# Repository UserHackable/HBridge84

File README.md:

# User Hackable HBridge84 Project

This is the User Hackable HBridge84 Project. 

It's purpose is to be a compact driver board for cars or robots. 

## Brains

The microcontroller used by this project is the ATtiny84 chip manufactured by Atmel. 
To program this chip using the [Arduino environment](https://www.arduino.cc/en/Main/Software), you will first need the [ATtiny board definition file](http://highlowtech.org/?p=1695) from [High Low Tech](http://highlowtech.org/). 

It includes:

* a C++ library for the Arduino IDE
* the Eagle Cad schematic and board layout files

# Arduino Installation

1. Start with a recent install of the [Arduino IDE](https://www.arduino.cc/en/Main/Software).
2. Install the [ATtiny library from High Low Tech](http://highlowtech.org/?p=1695).
3. Make sure you have an AVR ICSP programmer like the [Sparkfun Pocket AVR Programmer](https://www.sparkfun.com/products/9825) with it's drivers installed. 
4. Install this library by placing this entire folder as a subfolder in your Arduino/libraries folder.

## HBridge84 

### Board dimensions

* (200000, 130000) original units
* (2.0000, 1.3000) inches
* (50.8000, 33.0200) mm

| Front | Back |
| --- | --- |
|  |  |

## RJ11Breakout 

### Board dimensions

* (70000, 70000) original units
* (0.7000, 0.7000) inches
* (17.7800, 17.7800) mm

| Front | Back |
| --- | --- |
|  |  |

## RJ11-ICSP-Breakout 

### Board dimensions

* (90000, 100000) original units
* (0.9000, 1.0000) inches
* (22.8600, 25.4000) mm

| Front | Back |
| --- | --- |
|  |  |

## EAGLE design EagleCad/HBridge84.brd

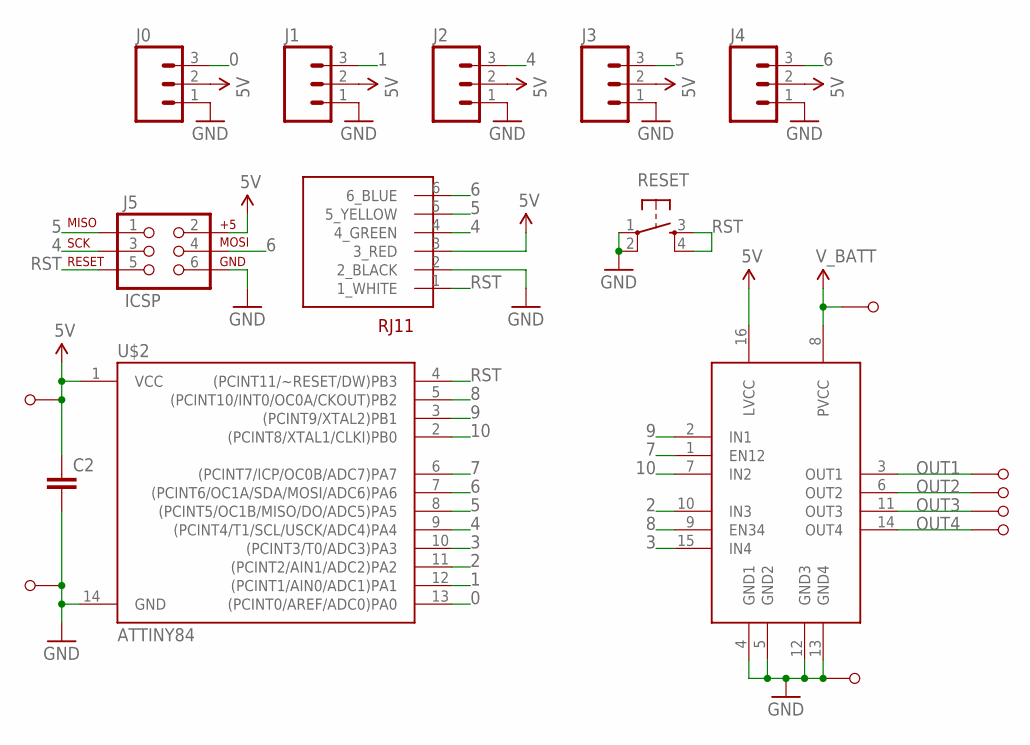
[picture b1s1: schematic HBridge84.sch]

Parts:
C2: CAPPTH; CAP-PTH-SMALL
J0, J1, J2, J3, J4: M03PTH; 1X03
J5: ICSP; 2X3-NS
RESET: TAC_SWITCHPTH; TACTILE-PTH
SN754410: SN754410; DIP16
U$1, U$3, U$4, U$5, U$6, U$8, U$9, U$10: M1; M1_NO_STRAIN
U$2: ATTINY84; DIL14
U$7: RJ12

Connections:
0: J0.3, U$2.13 ((PCINT0/AREF/ADC0)PA0)
1: J1.3, U$2.12 ((PCINT1/AIN0/ADC1)PA1)
2: SN754410.10 (IN3), U$2.11 ((PCINT2/AIN1/ADC2)PA2)
3: SN754410.15 (IN4), U$2.10 ((PCINT3/T0/ADC3)PA3)
4: J2.3, J5.3 (SCK), U$2.9 ((PCINT4/T1/SCL/USCK/ADC4)PA4), U$7.4 (4_GREEN)
5: J3.3, J5.1 (MISO), U$2.8 ((PCINT5/OC1B/MISO/DO/ADC5)PA5), U$7.5 (5_YELLOW)
5V: C2.1, J0.2, J1.2, J2.2, J3.2, J4.2, J5.2 (V+), SN754410.16 (LVCC), U$2.1 (VCC), U$7.3 (3_RED), U$10.P$1
6: J4.3, J5.4 (MOSI), U$2.7 ((PCINT6/OC1A/SDA/MOSI/ADC6)PA6), U$7.6 (6_BLUE)
7: SN754410.1 (EN12), U$2.6 ((PCINT7/ICP/OC0B/ADC7)PA7)
8: SN754410.9 (EN34), U$2.5 ((PCINT10/INT0/OC0A/CKOUT)PB2)
9: SN754410.2 (IN1), U$2.3 ((PCINT9/XTAL2)PB1)
10: SN754410.7 (IN2), U$2.2 ((PCINT8/XTAL1/CLKI)PB0)
GND: C2.2, J0.1, J1.1, J2.1, J3.1, J4.1, J5.6 (GND), RESET.1, RESET.2, SN754410.4 (GND1), SN754410.5 (GND2), SN754410.12 (GND3), SN754410.13 (GND4), U$2.14 (GND), U$7.2 (2_BLACK), U$8.P$1, U$9.P$1
OUT1: SN754410.3 (OUT1), U$1.P$1
OUT2: SN754410.6 (OUT2), U$3.P$1
OUT3: SN754410.11 (OUT3), U$4.P$1
OUT4: SN754410.14 (OUT4), U$5.P$1
RST: J5.5 (RST), RESET.3, RESET.4, U$2.4 ((PCINT11/~RESET/DW)PB3), U$7.1 (1_WHITE)
V_BATT: SN754410.8 (PVCC), U$6.P$1

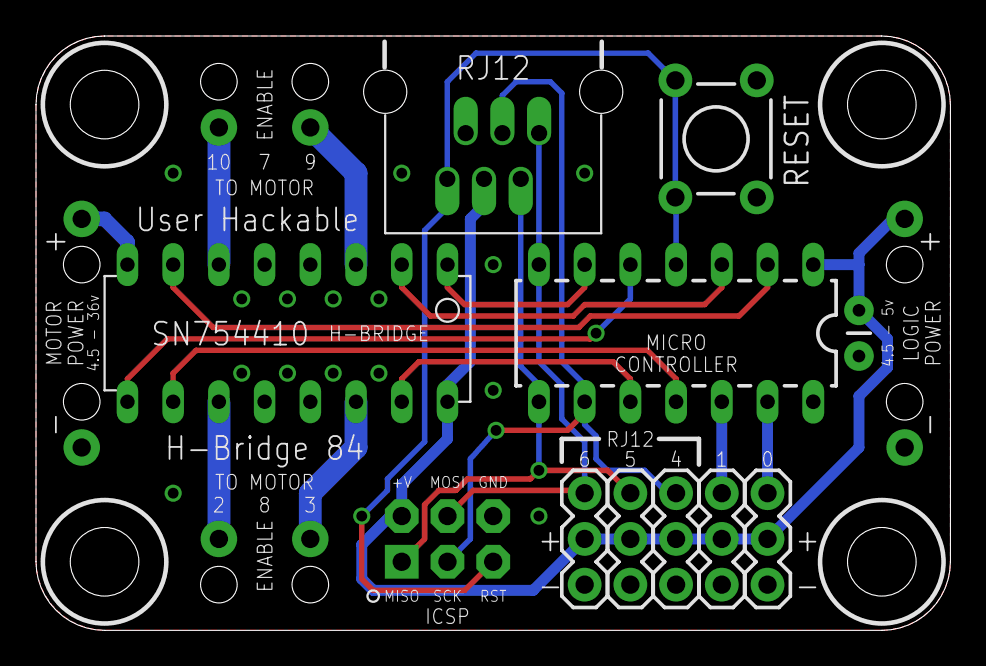
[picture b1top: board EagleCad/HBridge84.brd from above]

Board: 2 copper layers, 50.8 x 33.0 mm, 19 parts (0 on the bottom side), 19 nets.

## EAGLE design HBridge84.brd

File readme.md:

# User Hackable HBridge84 Project

This is the User Hackable HBridge84 Project. 

It's purpose is to be a compact driver board for cars or robots. 

## Brains

The microcontroller used by this project is the ATtiny84 chip manufactured by Atmel. 
To program this chip using the [Arduino environment](https://www.arduino.cc/en/Main/Software), you will first need the [ATtiny board definition file](http://highlowtech.org/?p=1695) from [High Low Tech](http://highlowtech.org/). 

It includes:

* a C++ library for the Arduino IDE
* the Eagle Cad schematic and board layout files

# Arduino Installation

1. Start with a recent install of the [Arduino IDE](https://www.arduino.cc/en/Main/Software).
2. Install the [ATtiny library from High Low Tech](http://highlowtech.org/?p=1695).
3. Make sure you have an AVR ICSP programmer like the [Sparkfun Pocket AVR Programmer](https://www.sparkfun.com/products/9825) with it's drivers installed. 
4. Install this library by placing this entire folder as a subfolder in your Arduino/libraries folder.

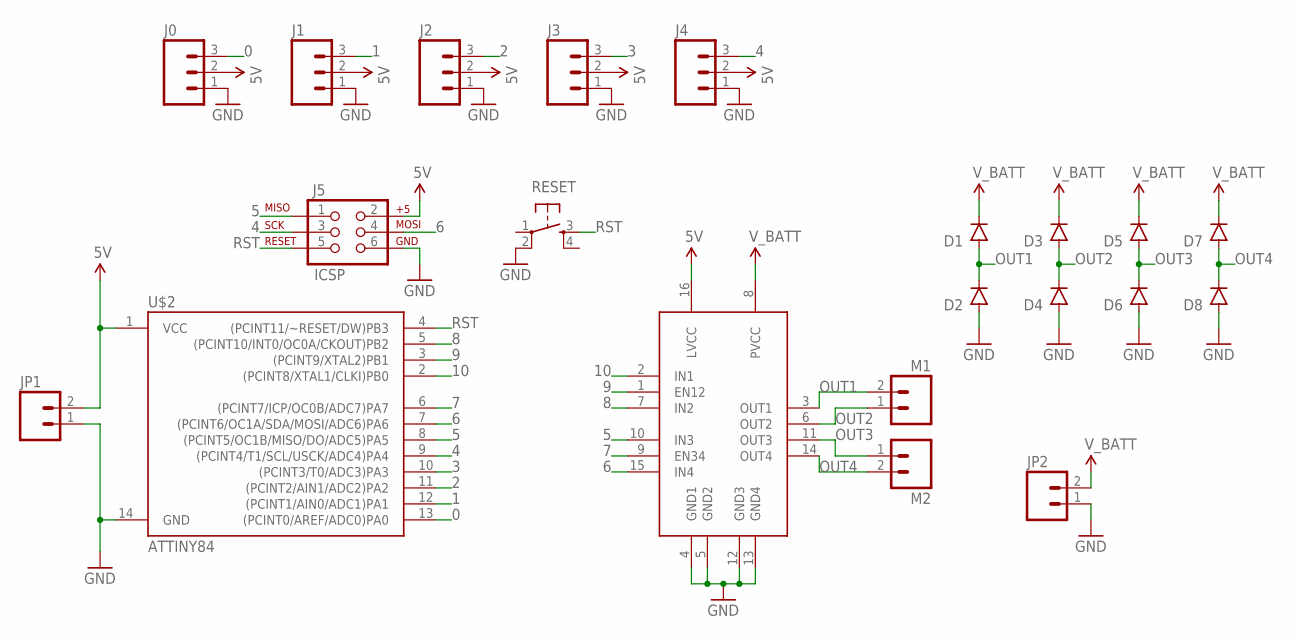
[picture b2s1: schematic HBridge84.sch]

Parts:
D1, D2, D3, D4, D5, D6, D7, D8: DIODEPTH; DIODE-1N4001
J0, J1, J2, J3, J4: M03PTH; 1X03
J5: ICSP; 2X3-NS
JP1, JP2: M02PTH; 1X02
M1, M2: M02PTH; 1X02
RESET: TAC_SWITCHPTH; TACTILE-PTH
SN754410: SN754410; DIP16
U$2: ATTINY84; DIL14

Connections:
0: J0.3, U$2.13 ((PCINT0/AREF/ADC0)PA0)
1: J1.3, U$2.12 ((PCINT1/AIN0/ADC1)PA1)
2: J2.3, U$2.11 ((PCINT2/AIN1/ADC2)PA2)
3: J3.3, U$2.10 ((PCINT3/T0/ADC3)PA3)
4: J4.3, J5.3 (SCK), U$2.9 ((PCINT4/T1/SCL/USCK/ADC4)PA4)
5: J5.1 (MISO), SN754410.10 (IN3), U$2.8 ((PCINT5/OC1B/MISO/DO/ADC5)PA5)
5V: J0.2, J1.2, J2.2, J3.2, J4.2, J5.2 (V+), JP1.2, SN754410.16 (LVCC), U$2.1 (VCC)
6: J5.4 (MOSI), SN754410.15 (IN4), U$2.7 ((PCINT6/OC1A/SDA/MOSI/ADC6)PA6)
7: SN754410.9 (EN34), U$2.6 ((PCINT7/ICP/OC0B/ADC7)PA7)
8: SN754410.7 (IN2), U$2.5 ((PCINT10/INT0/OC0A/CKOUT)PB2)
9: SN754410.1 (EN12), U$2.3 ((PCINT9/XTAL2)PB1)
10: SN754410.2 (IN1), U$2.2 ((PCINT8/XTAL1/CLKI)PB0)
GND: D2.A, D4.A, D6.A, D8.A, J0.1, J1.1, J2.1, J3.1, J4.1, J5.6 (GND), JP1.1, JP2.1, RESET.2, SN754410.4 (GND1), SN754410.5 (GND2), SN754410.12 (GND3), SN754410.13 (GND4), U$2.14 (GND)
OUT1: D1.A, D2.C, M1.2, SN754410.3 (OUT1)
OUT2: D3.A, D4.C, M1.1, SN754410.6 (OUT2)
OUT3: D5.A, D6.C, M2.1, SN754410.11 (OUT3)
OUT4: D7.A, D8.C, M2.2, SN754410.14 (OUT4)
RST: J5.5 (RST), RESET.3, U$2.4 ((PCINT11/~RESET/DW)PB3)
V_BATT: D1.C, D3.C, D5.C, D7.C, JP2.2, SN754410.8 (PVCC)

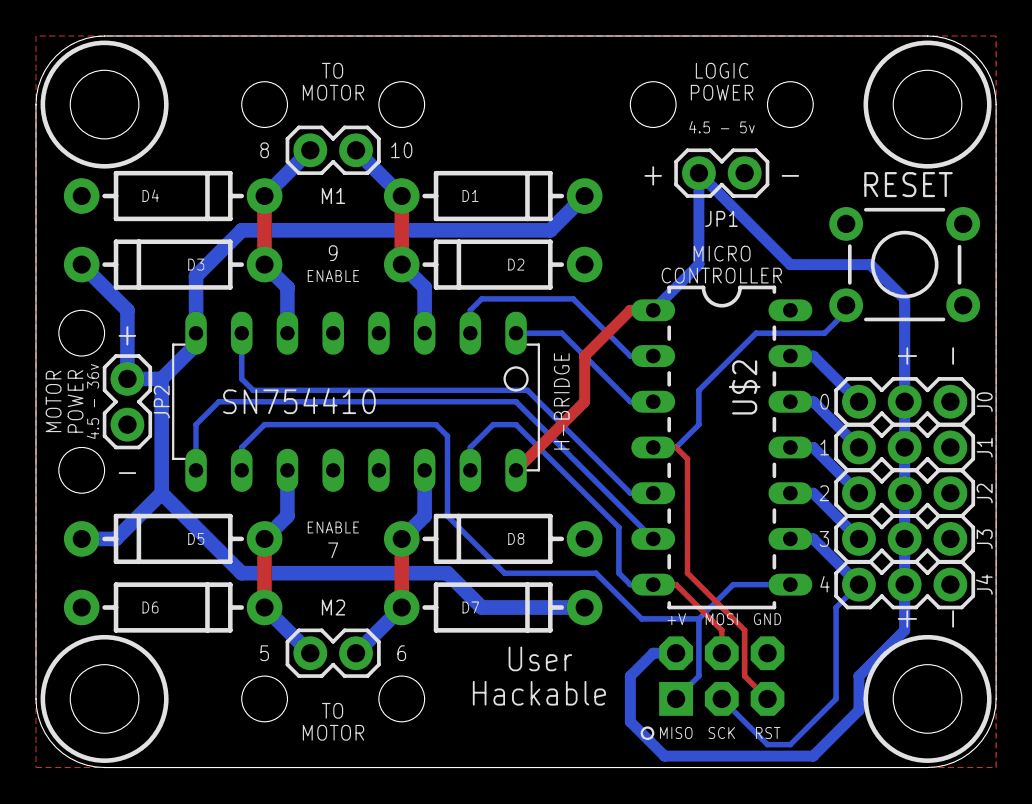
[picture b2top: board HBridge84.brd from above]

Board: 2 copper layers, 53.3 x 40.6 mm, 21 parts (0 on the bottom side), 19 nets.

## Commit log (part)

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2016-03-11 first_commit
2016-03-11 updating readme
2016-03-11 updating examples
2016-03-11 adding eagle files
2016-03-11 changing backward to reverse
2016-03-11 all examples work
2016-03-12 updating pcb image
2016-03-12 give examples meaningful names
2016-03-26 adding in md files
2016-03-26 updating readme.md
2016-03-26 foobar
2016-03-26 updating ICSP breakout
2016-03-26 updating README.rb
2016-03-26 fleeble
2016-03-26 update ICSP breakout
2016-03-26 adding in gerber zip files
2016-03-26 fixing ICSP breakout border
2016-04-06 updating
2016-04-07 from Makefile
2016-04-22 added bare basic
2016-05-06 Uploaded line follower
2016-05-06 added linefollower

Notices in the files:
parts and their libraries:
SparkFun-Connectors: Licensing: Creative Commons ShareAlike 4.0 International - https://creativecommons.org/licenses/by-sa/4.0
